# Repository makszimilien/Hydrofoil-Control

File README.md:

# Hydrofoil Control R5.5 — one Wi-Fi for normal setup

**October 28, 2026 · experimental field-test candidate. Built and host-tested; R5.5 is not yet installed or tested on the boat.** The two project boards still run R5.4.1. R5.5 is a development revision of this fork, not an upstream official release.

R5.5 brings everyday two-board setup onto the master's Wi-Fi: control, tuning, calibration, live readings and actual saved settings. It retains application-only Wi-Fi updates and the 30-second diagnostic recorder. Each board still runs its own sensor and servo loop; the master is a configuration interface, not a source of continuous servo commands for the slave.

## At the water's edge

After both boards have R5.5 and have been paired in Device setup, join the **master's Wi-Fi** and open **http://192.168.4.1/**. The heading shows the actual network-name suffix and Master/Slave role; suffixes are discovered, never hardcoded.

- **Control:** see each board's state and Run/Pause both. Amber means paused; red means a fault or missing current status. Text identifies the state as well as color. Pause switches servo output off; it does not change saved tuning. Normal control starts automatically at power-on when settings and calibration are usable.
- **Set up & tune:** choose either board's name button, or Both. Individual views show that board's actual saved settings, fresh sensor/servo readings, calibration, Run/Pause and direction. Edits remain drafts until Apply. Both applies common P/I/D, Set Point, receiver influence and, by default, travel bounds. Different saved values remain blank and marked Different until a common value is entered.
- **Test:** center both at exactly **1500 microseconds**, or enter a reference pulse for one servo. Center ignores trim and direction. Manual values use the receiving board's saved endpoint order: reversed boards mirror around 1500, so reference 1600 becomes actual 1400. The actual command is displayed. Manual tests bypass travel limits, so begin near center and work outward while checking the linkage. End test & run/pause returns to normal operation or switches output off.

Calibration is individual: select a board, Start, move its sensor from fully out of water to the intended immersion depth and back a few times, then Finish & save. A usable candidate replaces that board's saved range; no usable new range retains the previous range. Finish leaves that board paused. A restarted/interrupted calibration needs Finish followed by Start for a new session. Calibration is never copied between boards.

Shared travel uses lower/upper bounds while retaining each board's direction. For example, 1200–1800 becomes 1800/1200 on a reversed board and 1200/1800 on a normal board. A travel change pauses the affected board; use Run in Control afterward. Shared saves are confirmed independently, not atomically or simultaneously. Unconfirmed means no matching reply was received; the change may have arrived. Inspect current readback before retrying. There is no automatic settings push at boot or pairing.

Normal operation always uses the water-height sensor. **Set Point** uses the calibrated 1000–2000 scale; 1500 is its midpoint. Receiver influence remains an optional offset to that target; 0% adds none and a stale receiver adds zero. Receiver-only mode is removed. Legacy mode fields remain in storage/protocol layouts and normalize to sensor control without rewriting other settings at boot.

## What still needs direct board Wi-Fi

Firmware updates, initial role/peer setup, recovery, detailed diagnostics and full 30-second recordings still use the board being accessed. The recorder is under Test → Recording & diagnostics and explicitly names its connected board. Both boards must have this R5.5 revision before relying on its remote setup, shared travel and name discovery.

## Sensor construction is fundamental

**The sensor strip must be electrically isolated at all costs.** Seal the sensing copper on both faces, every edge, both ends and the wire junction, including its backside against the printed mast. The ground electrode intentionally contacts water.

Front-only tape and longer timeouts did not cure immersion-dependent failures. Insulating both faces produced 17,732 good readings and zero timeouts across six user recordings; a separate helper capture brings the unique total to 20,681. These were T1/50 ms diagnostic tests, not R5.5 tests. The precise ingress route was not proven. See [sensor findings](SENSOR-INSULATION.md). Coating abrasion, long soaking and salt-water operation remain to be checked.

## Build and checks

The target is ESP32-C3, PlatformIO `esp32-c3-devkitm-1`, `espressif32@6.12.0`, Arduino ESP32 2.0.17. Tested with PlatformIO Core 6.2.0. Install PlatformIO in a Python virtual environment, then:

```sh
pio run -e esp32-c3-devkitm-1
python3 tests/run_all_r55_tests.py
```

Tests require Python 3, clang++ with UndefinedBehaviorSanitizer and Node.js. Build first to resolve QuickPID and ArduinoJson. [Test instructions](tests/README.md) describe coverage and portability adjustments. [TEST-RESULTS.md](TEST-RESULTS.md) distinguishes software checks from physical evidence. [BUILD-MANIFEST.json](BUILD-MANIFEST.json) records the retained candidate binary, dependency versions and firmware-input hashes. Build-path/timestamp differences can change a rebuilt binary's hash.

The application is `.pio/build/esp32-c3-devkitm-1/firmware.bin`. UI assets are embedded in the application; `data/` contains matching source and generic blank credentials/empty peers. **Do not upload the filesystem over an existing board's saved configuration.** Existing-device installation is application-only after checking exact identity, chip, partition capacity and current firmware. Normal control may start after the update reboot, just as it does at power-on. No universal uploader or complete-flash rollback is included.

## Timing and limits

Normal sensing retains the approximately **2 ms** bounded acquisition, target 500 Hz sampling and 100 Hz PID cadence. Twenty fresh successful readings are required after a timeout before filtered control resumes. A normal-control sensor timeout holds the last commanded servo pulse; it does not automatically switch output off. The separate 30-second recorder targets 100 Hz and records actual timestamps. Diagnostic T1/50 ms, T2/500 ms and creator-style C1 experiments are retired and are not this controller.

Remote snapshots expire after 3.5 seconds. Stale state is shown as unconfirmed and editing is disabled. Explicit Apply, calibration and test commands use matched acknowledgements, bounded retries and duplicate/stale-command checks. A displayed servo pulse is a command, not measured shaft position or foil angle.

R5.5 has no physical two-board, cold-power-cycle, loaded or on-water acceptance yet. Its inherited HTTP/OTA access and ESP-NOW trust model are for a controlled development setup, not an authenticated deployment. [FIELD-TEST-PLAN.md](FIELD-TEST-PLAN.md) is the next acceptance record, not a claim that testing has occurred.

## History and next work

[CHANGELOG.md](CHANGELOG.md) records R5 through R5.5 and the retired sensing experiments. [ROADMAP.md](ROADMAP.md) separates immediate field acceptance from possible later improvements. The working R5.4.1 setup already demonstrated calibration, confirmed tuning transfer and the intended opposite electrical pulses producing the same physical AoA direction. Those observations do not validate the new R5.5 remote protocol on hardware.

## Attribution and license

Based on Tamas Nagy's Hydrofoil Control. The upstream [LICENSE](LICENSE) is retained verbatim. Its title says MIT License, but its text includes additional non-commercial, attribution and hardware-exclusion conditions; this project does not relicense the original software or hardware. PlatformIO libraries retain their own licenses.

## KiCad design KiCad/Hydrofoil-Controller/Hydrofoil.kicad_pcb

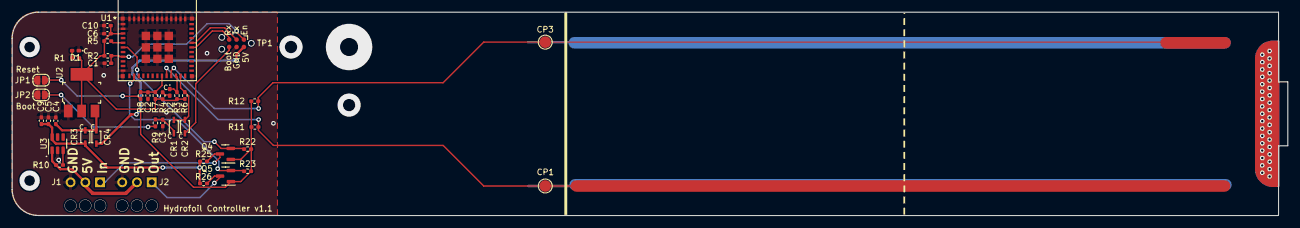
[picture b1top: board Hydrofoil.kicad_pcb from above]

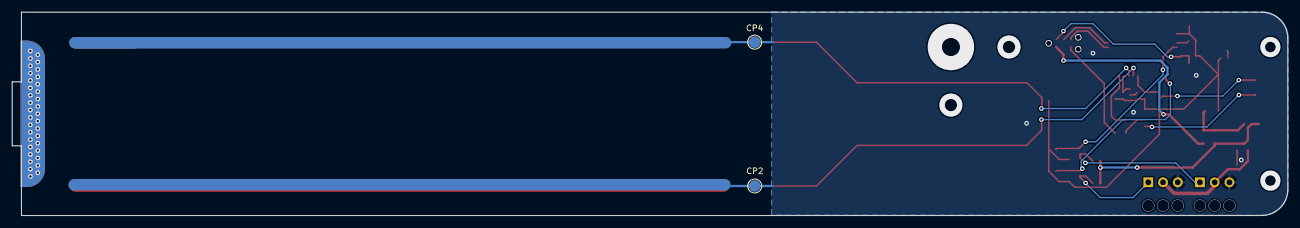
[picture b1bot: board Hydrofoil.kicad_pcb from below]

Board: 2 copper layers, 219.6 x 35.0 mm, 44 parts (2 on the bottom side), 26 nets.

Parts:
C1, C2, C3: 1u; C_0402_1005Metric_Pad0.74x0.62mm_HandSolder
C4, C5, C6, C9, C10: 10u; C_0402_1005Metric_Pad0.74x0.62mm_HandSolder
CP1, CP2: Long Probe; TestPoint_Pad_D2.0mm
CP3, CP4: Short Probe; TestPoint_Pad_D2.0mm
CR1, CR2, CR3, CR4: CUS08F30_H3F; USC_TOS
D1: Yellow; LED_0402_1005Metric_Pad0.77x0.64mm_HandSolder
D2: Red; LED_0402_1005Metric_Pad0.77x0.64mm_HandSolder
J1, J2: Conn_01x03_Pin; Solder_Connector
JP1: Reset Settings; SolderJumper-2_P1.3mm_Open_RoundedPad1.0x1.5mm
JP2: Boot; SolderJumper-2_P1.3mm_Open_RoundedPad1.0x1.5mm
Q4, Q5: BSS138; SOT-23
R1, R4, R8, R9: 1k; R_0402_1005Metric_Pad0.72x0.64mm_HandSolder
R2, R3, R5, R6, R7, R10, R22, R23, R25, R26: 10k; R_0402_1005Metric_Pad0.72x0.64mm_HandSolder
R11, R12: 1.4M; R_0402_1005Metric_Pad0.72x0.64mm_HandSolder
TP1: Tag-Connect_TC2030-IDC-NL_2x03_P1.27mm_Vertical
U1: ESP32-C3-MINI-1-N4; ESP32-C3-MINI-1_EXP
U2: LD1117S33CTR; SOT-223
U3: TPS22917DBV; SOT-23-6

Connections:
+3.3V: C6.1, C10.1, Q4.1 (G), Q5.1 (G), R1.1, R2.1, R3.1, R4.1, R5.1, R6.1, R7.1, R11.1, R12.1, R22.1, R23.1, U1.3 (3V3), U2.2 (VOUT), U2.4 (VOUT)
+5V: C5.1, C9.1, CR3.2, R25.1, R26.1, U3.6 (VOUT)
+5V-Prog: CR4.2, TP1.2
/+5V-Logic: C4.1, CR3.1, CR4.1, U2.3 (VIN)
/+5V-Raw: J1.2, J2.2, R10.2, U3.1 (VIN)
Cap-Long: CP1.1, R11.2, U1.20 (IO6)
Cap-Ref: CP3.1, R12.2, U1.21 (IO7)
ESP-Boot: CR2.1, TP1.6
ESP-En: C1.1, R2.2, TP1.1, U1.8 (EN)
ESP-Rx: TP1.5, U1.30 (RXD0)
ESP-Tx: TP1.3, U1.31 (TXD0)
GND: C1.2, C2.2, C3.2, C4.2, C5.2, C6.2, C9.2, C10.2, CP2.1, CP4.1, D1.1 (K), J1.3, J2.3, JP1.2 (B), JP2.2 (B), TP1.4, U1.1 (GND), U1.2 (GND), U1.11 (GND), U1.14 (GND), U1.36 (GND), U1.37 (GND), U1.38 (GND), U1.39 (GND), U1.40 (GND), U1.41 (GND), U1.42 (GND), U1.43 (GND), U1.44 (GND), U1.45 (GND), U1.46 (GND), U1.47 (GND), U1.48 (GND), U1.49 (GND), U1.50 (GND), U1.51 (GND), U1.52 (GND), U1.53 (GND), U1.54 (GND), U1.55 (GND), U1.56 (GND), U1.57 (GND), U1.58 (GND), U1.59 (GND), U1.60 (GND), U1.61 (GND), U2.1 (GND), U3.2 (GND)
Input-Boot: CR1.2, CR2.2, R6.2, U1.23 (IO9)
Input-Reset: C2.1, R7.2, R8.1, U1.19 (IO5)
unnamed: C3.1, CR1.1, R9.1
unnamed: D1.2 (A), R1.2
unnamed: D2.2 (A), R4.2
unnamed: JP1.1 (A), R8.2
unnamed: JP2.1 (A), R9.2
unnamed: R5.2, U1.5 (IO2)
unnamed: R10.1, U3.3 (ON)
PWM-In-HV: J1.1, Q4.3 (D), R25.2
PWM-In-LV: Q4.2 (S), R22.2, U1.6 (IO3)
PWM-Out-HV: J2.1, Q5.3 (D), R26.2
PWM-Out-LV: Q5.2 (S), R23.2, U1.13 (IO1)
User-LED: D2.1 (K), R3.2, U1.22 (IO8)

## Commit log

2023-08-18 Add PID (not working)
2023-08-19 Use PID for servo control
2023-08-21 Add external control using PWM input
2023-08-22 Add pulseIn timeout to reduce cycle time, fix setpoint value definition
2023-08-24 Create new branch for Pro Micro
2023-08-27 Use external ADC
2023-08-27 Use extarnal ADC, remove commented lines
2023-08-31 Add external ADC (ADS1115), read from A0 and A1
2023-09-01 Use 2 chs on the ADC
2023-09-02 Calculate sensorRatio
2023-09-02 Fix float division
2023-09-02 Use sensor for servo control
2023-09-07 Add KiCad files
2023-09-07 Start routing on the PCB
2023-09-10 Finalize edgecut, device arrangement, wiring
2023-09-10 Add probe-traces
2023-09-14 Initialize codebase for ESP32
2023-09-14 Add websocet
2023-09-15 Fix handling Slave input
2023-09-18 Setup First-Start and Master hotspots
2023-09-18 Modify WiFi manager (remove SSID and password, add MAC address
2023-09-19 Remove ArduinoOTA, add mDNS
2023-09-19 Fix websocket issue
2023-09-20 Add slider, store value in config.json, set output accordingly, send value on ws
2023-09-21 Fix storing and reclaiming slider value
2023-09-21 Update slider position based on stored value
2023-09-21 Read submitted MAC, start reading array from JSON
2023-09-22 Finalize JSON array read/write
2023-09-22 Fix JSON array write issue
2023-09-23 Handle MAC string conversion to hex
2023-09-23 Show added devices on control page
2023-09-23 Clean up code (a little)
2023-09-23 Fix mDNS issue
2023-09-23 Add ESP-NOW funcionality (receiver does not work), convert strings to bool
2023-09-24 Modify code to help debug ESP-NOW (0x3069): ESPNOW peer is not found
2023-09-25 Fix ESP-NOW master send issue
2023-09-25 User user input MAC for adding slave device
2023-09-26 Store MAC addresses in array properly
2023-09-27 Add sliders, start rewriting slider value and MAC address handling
2023-09-29 Finalize data handling(server side), modify FS JSON handling (do not override existing)
2023-09-29 Fix writing JSON array to SPIFFS
2023-09-29 Check if MAC was already added
2023-09-29 Finalize MAC address handling
2023-09-29 Send data to peers on ESP-NOW
2023-10-06 Add PS to the curcuit, change PCB outline
2023-10-07 Add ESP32-C3-Mini
2023-10-07 Add level shifters
2023-10-08 Change resistor values
2023-10-08 Change reverse polarity protection, start the PCB design
2023-10-13 Use load switch, fix TC2030 pins, fix strapping pins
2023-10-13 Organize parts on the PCB
2023-10-15 Finish PCB layout, start PCB routing
2023-10-18 Finish routing
2023-10-18 Generate fabrication files
2023-10-21 Add MPN to BOM, create PCBWay specific fabrication files
2023-10-29 Refactor the handling of ESP-NOW communication
2023-10-29 Finish refactoring main.cpp
2023-10-29 Make sendEspNow function failsafe
2023-10-30 Fix Websocket loading issue
2023-10-31 Clean up the handling of SPIFFS
2023-10-31 Clear up style.css, use it for wifimanager
2023-11-02 Add device reset functionality
2023-11-03 Change reset times, set all parameters to default when resetting device
2023-11-03 Use float variables for PID parameters, set input ranges
2023-11-06 Fix LED's PNs
2023-11-11 Add external ADC, read values on 2 channels
2023-11-11 Read PWM input from receiver
2023-11-11 Use interrupt instead of pulseIn to reduce cycle time
2023-11-24 Change environment to ESP32-C3
2023-11-25 Fix I2C issues, fix device reset
2023-11-25 disable dtr & rts on bootstrap
2023-12-01 Widen servo traces, add C to slikscreen, replace LEDs to 0402
2023-12-01 Add missing silkscreen texts
2023-12-02 Fix ADC reading issue
2023-12-11 Calculate ratio from sensor readings
2023-12-19 Add capacitive sensor, organize KiCad folder
2023-12-19 Fix sensor debug serial messages
2024-01-19 update platformio settings, test new meaasurement method
2024-01-19 fix monitor speed
2024-01-20 Remove ADC, add capacitance measurement
2024-01-20 Use interrupt for measurement, delete sensor pcb
2024-01-23 Remove ADC from PCB
2024-01-26 Add capacitance measurement to the PCB
2024-02-03 Refactor measurement, use only one struct for ESP-NOW
2024-02-03 Fix the listing of the slave devices on the UI
2024-02-04 Implement PID controller
2024-02-04 Fix PID parameter issues
2024-02-04 Implement PWM signal input, modify setpoint based on reading
2024-02-04 Fix servo output issues
2024-02-05 Calculate control value in the PWM In interrupt
2024-02-05 Fix data refresh issues on the page
2024-02-17 Receive and show process values at the client
2024-02-17 Send process values to client via websocket
2024-03-01 Reload page if no response for WS request
2024-03-01 Add new parameters to the log, change appearance
2024-03-02 Update PID tunings when parameters changed
2024-03-02 Fix setting min and max values on the measurement scale
2024-03-03 Change WS connection error handling
2024-03-03 Use non-blocking delay
2024-03-03 Fix non-blocking delay, set measuring freq. to 200 Hz
2024-03-14 Use POST instead of WS for WIFI manager
2024-03-15 Remove WS, use HTTP GET for sliders, implement PID enable functionality
2024-03-15 Debounce slider events, comment out Serial.print calls
2024-03-17 Remove servoMid param, center servo when PID disabled
2024-03-17 Fix servo min & max handling on slave devices
2024-03-17 Fix rebooting issue
2024-03-17 Send MAC addresses via HTTP_GET, blink the LED when resetting device
2024-03-17 Display slave device's MAC addresses on the page
2024-03-17 Send process values to the client, show them on the page
2024-03-23 Clear up code
2024-03-23 Add PWM input effect slider and functionality
2024-03-23 Fix storing servoPos, set tickers properly
2024-03-23 Improve on exluding exreme measurement values
2024-03-23 Add disable Wifi functionality
2024-03-23 Do not init ESP-NOW when Wifi disabled
2024-03-24 Send setpoint to the page
2024-04-25 Use busy loop insted of interrupt to finish cap measurement
2024-05-01 Delay page reload after POSTing MAC address (iPhone issue)
2024-05-08 Send data for the Python script, use writeMicroseconds
2024-05-08 Use writeMicroseconds for the sevo, change WD timeout to 4s
2024-05-12 Remove process data from the page, use writeMicroseconds, change input value validation
2024-05-18 Change handling minMeasured
2024-05-19 Change handling min- and maxMeasured values, use delayWhileMicros
2024-05-19 Decrease the no. of measurements for calculating median
2024-05-20 Reduce measurement and PID calculation time
2024-06-16 Use us instead of degree for servo control
2024-06-16 Modify logPid function
2024-06-16 Add encoder functionality and distance measurement
2024-06-18 Change Pid Sample Time to 10000us
2024-06-18 Refactor PID control mode to use timer instead of automatic
2024-06-18 Change the reset default values, change logPid values, fix sending variables to the page
2024-06-18 Change baud rate to 115200
2024-06-18 Change PID mode, change default reset values, remove logger the functions, fix sending servo params to the page
2024-06-25 Put back serial logger, use fixed values for min- and maxMeasured
2024-06-25 Use one ticker for calculating position and PID
2024-06-26 Improve upon CSS design
2024-06-29 Improve upon adding new slave device
2024-06-30 Use MAC address for unique SSID, use fixed channel, fix wifimanager css
2024-06-30 Fix PWM input issue
2024-07-03 Add board selector input to the page
2024-07-03 Receive boardSelector value on sever side
2024-07-05 Add boardSelector to get-settings, add new datastruct for control params
2024-07-07 Handle select board requests
2024-07-07 Read/write json boardsParams to flash memory
2024-07-07 Use boardParams struct for board init, modify resetDevice
2024-07-07 Change targeting servo for setting end positions
2024-07-09 Add MAC parameter to the sendEspNow function
2024-07-09 Add the datastruct to sendEspNow function as a parameter
2024-07-09 Send data to the second slave device
2024-07-09 Add Remove All Slaves button to the page
2024-07-09 Send params to slaves at startup, move servo to min/max pos onslaves
2024-07-10 Change handling servoTarget, fix showing end positions
2024-07-10 Remove old config.json
2024-07-10 Store and retreive params on slave devices
2024-07-13 Append board selector list only when slave is added
2024-07-16 Fix PWM input (PID controller ignoring setpoint value)
2024-07-16 Turn on the LED when input close to setpoint
2024-08-13 Add manual RC control functionality
2024-08-13 Clean css files, handle ssid and password inputs
2024-08-14 Clean Wifimanager page
2024-08-14 Add Upload mode (no AP mode, no OTA)
2024-08-15 Fix the device reset method
2024-08-15 Start device in Station mode and connect to the given SSID when device started in Upload mode
2024-08-15 Add Arduino OTA functionality
2024-08-15 Reset upload, ssid and password variables in resetDevice
2024-08-16 Add server availability check
2024-08-23 Start self test functionality, add ticker for measurement, read serial
2024-08-23 Handle received value, move the servo then start the measurement
2024-09-01 Send measured values via Serial
2024-10-10 Fix self-test probe measurement issue
2024-12-05 Change pMode, add serial log
2024-12-08 Change pMode and AwMode
2024-12-21 Chenge PID limits
2024-12-21 Add Calibration enable switch
2024-12-21 Add min and maxMeasured to datastruct
2024-12-21 Add default values to the new variables
2024-12-22 Create LICENSE
2024-12-22 Change how servoMin and Max values are handled
2024-12-22 Add new variables to file handling
2024-12-22 Add calibration functionality to master
2024-12-22 Add calibration functionality to the slave
2024-12-22 Inhibit interrupt during measurement
2024-12-22 Rename hotspot, change state of the enable sliders on click
2024-12-22 Change measurement and logging time
2025-01-11 Update License
2025-02-08 Fix self test issue
2025-02-14 Fix PID Output scaling issue
2025-02-15 Calculate median of the PWM input values
2025-02-15 Remove median calculation from PWM input
2025-02-18 Add RMT for reading PWM (not working)
2025-02-25 Use a ticker to read ring buffer for RMT
2025-02-25 Finish PWM input handling, clean up code
2025-04-29 Update default endpoint values, change calibration starting values
2025-09-14 Add logging
2025-09-14 Log received data
2025-09-14 Check data length
2025-09-14 Always save min and max measured
2025-09-14 Log data movement
2025-09-14 Check if it enters calibration
2025-09-14 Change min and maxMeasured handling
2025-09-14 Store min and maxMeasured values separately for slaves
2025-09-14 Fix slave calibration issue
2025-10-11 Fix RMT settings, empty the ring buffer
2025-10-11 Remove serial logging
2025-10-12 Add serial logging
2025-10-14 Remove RMT
2025-10-19 Revert "Remove RMT"
    This reverts commit 8116ec5a7e190efa0af56f1760e2cb07dae60e8a.
2025-10-19 Change RMT parameters, read latestvalue only
2025-10-23 Add data validation to ESP-NOW onDataRecv
2025-11-03 Change servoEndPos delay to non-blocking timeout
